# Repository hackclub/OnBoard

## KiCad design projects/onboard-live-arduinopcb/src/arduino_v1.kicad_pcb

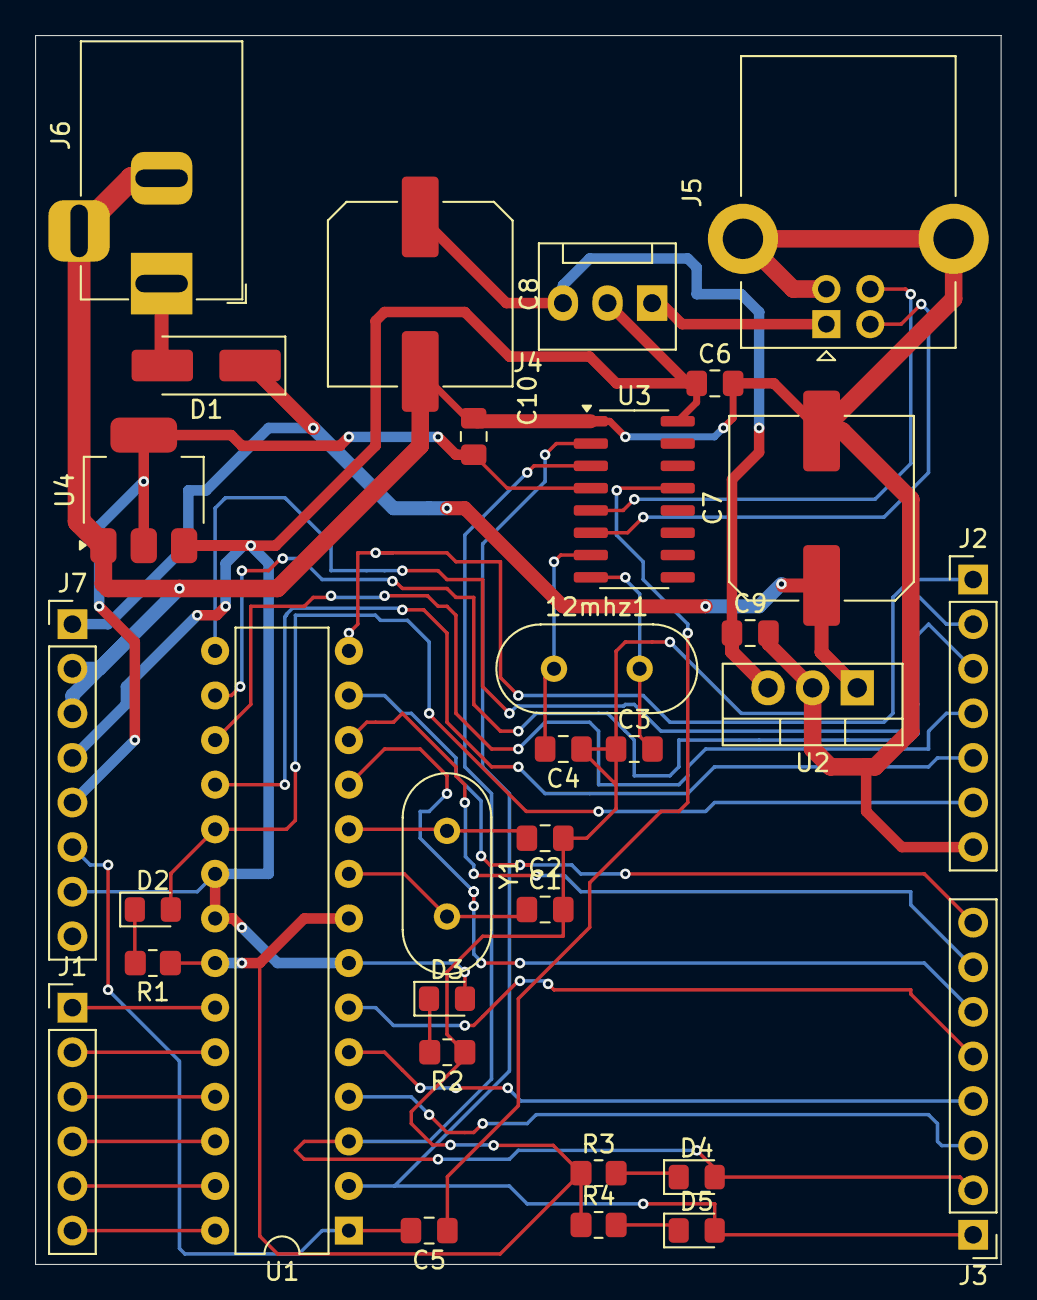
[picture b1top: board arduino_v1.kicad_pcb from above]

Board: 2 copper layers, 55.0 x 70.0 mm, 32 parts (0 on the bottom side), 39 nets.

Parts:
12mhz1: Crystal; Crystal_HC49-4H_Vertical
C1, C2, C3, C4: 22pf; C_0805_2012Metric_Pad1.18x1.45mm_HandSolder
C5, C6, C9, C10: 100nF; C_0805_2012Metric_Pad1.18x1.45mm_HandSolder
C7, C8: 100uF; C_Elec_10x10.2
D1: IN4007; D_SMA_Handsoldering
D2, D3, D4, D5: LED; LED_0805_2012Metric_Pad1.15x1.40mm_HandSolder
J1: Conn_01x06_Pin; PinHeader_1x06_P2.54mm_Vertical
J2: Conn_01x07_Pin; PinHeader_1x07_P2.54mm_Vertical
J3, J7: Conn_01x08_Pin; PinHeader_1x08_P2.54mm_Vertical
J4: Conn_01x03_Pin; FanPinHeader_1x03_P2.54mm_Vertical
J5: USB_B; USB_B_Lumberg_2411_02_Horizontal
J6: Barrel_Jack_Switch; BarrelJack_Horizontal
R1, R2, R3, R4: 330R; R_0805_2012Metric_Pad1.20x1.40mm_HandSolder
U1: ATmega328-P; DIP-28_W7.62mm
U2: LM7805_TO220; TO-220-3_Vertical
U3: CH340G; SOIC-16_3.9x9.9mm_P1.27mm
U4: AMS1117-3.3; SOT-223-3_TabPin2
Y1: Crystal; Crystal_HC49-4H_Vertical

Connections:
3.3V: C10.1, J7.5, U3.4 (V3), U4.2 (VO)
5V: C8.1, C9.1, J4.3, U2.3 (VO)
5VU: J4.1, J5.1 (VBUS)
A0: J1.1, U1.23 (PC0)
A1: J1.2, U1.24 (PC1)
A2: J1.3, U1.25 (PC2)
A3: J1.4, U1.26 (PC3)
A4: J1.5, U1.27 (PC4)
A5: J1.6, U1.28 (PC5)
D2: J3.3, U1.4 (PD2)
D3: J3.4, U1.5 (PD3)
D4: J3.5, U1.6 (PD4)
D5: J3.6, U1.11 (PD5)
D6: J3.7, U1.12 (PD6)
D7: J3.8, U1.13 (PD7)
D8: J2.1, U1.14 (PB0)
D9: J2.2, U1.15 (PB1)
D10: J2.3, U1.16 (PB2)
D11: J2.4, U1.17 (PB3)
D12: J2.5, U1.18 (PB4)
D13: D2.2 (A), J2.6, U1.19 (PB5)
GND: C1.2, C2.1, C3.1, C4.1, C6.2, C7.2, C8.2, C9.2, C10.2, J2.7, J5.4 (GND), J5.5 (Shield), J6.2, J6.3, J7.2, J7.3, R1.1, R2.1, R3.1, R4.1, U1.8 (GND), U1.22 (GND), U2.2 (GND), U3.1 (GND), U4.1 (GND)
unnamed: D1.2 (A), J6.1
unnamed: D2.1 (K), R1.2
unnamed: D3.1 (K), R2.2
unnamed: D4.1 (K), R3.2
unnamed: D5.1 (K), R4.2
unnamed: J5.3 (D+), U3.5 (UD+)
unnamed: J5.2 (D-), U3.6 (UD-)
unnamed: C1.1, U1.9 (XTAL1/PB6), Y1.2
unnamed: C2.2, U1.10 (XTAL2/PB7), Y1.1
unnamed: 12mhz1.1, C4.2, U3.7 (XI)
unnamed: 12mhz1.2, C3.2, U3.8 (XO)
unnamed: C5.1, U3.13 (~DTR)
RST: C5.2, J7.6, U1.1 (~RESET/PC6)
RXD: D5.2 (A), J3.1, U1.2 (PD0), U3.2 (TXD)
TXD: D4.2 (A), J3.2, U1.3 (PD1), U3.3 (RXD)
VCC: C6.1, D3.2 (A), J4.2, J7.4, J7.7, U1.7 (VCC), U1.20 (AVCC), U1.21 (AREF), U3.16 (VCC), U4.3 (VI)
VIN: C7.1, D1.1 (K), J7.1, U2.1 (VI)

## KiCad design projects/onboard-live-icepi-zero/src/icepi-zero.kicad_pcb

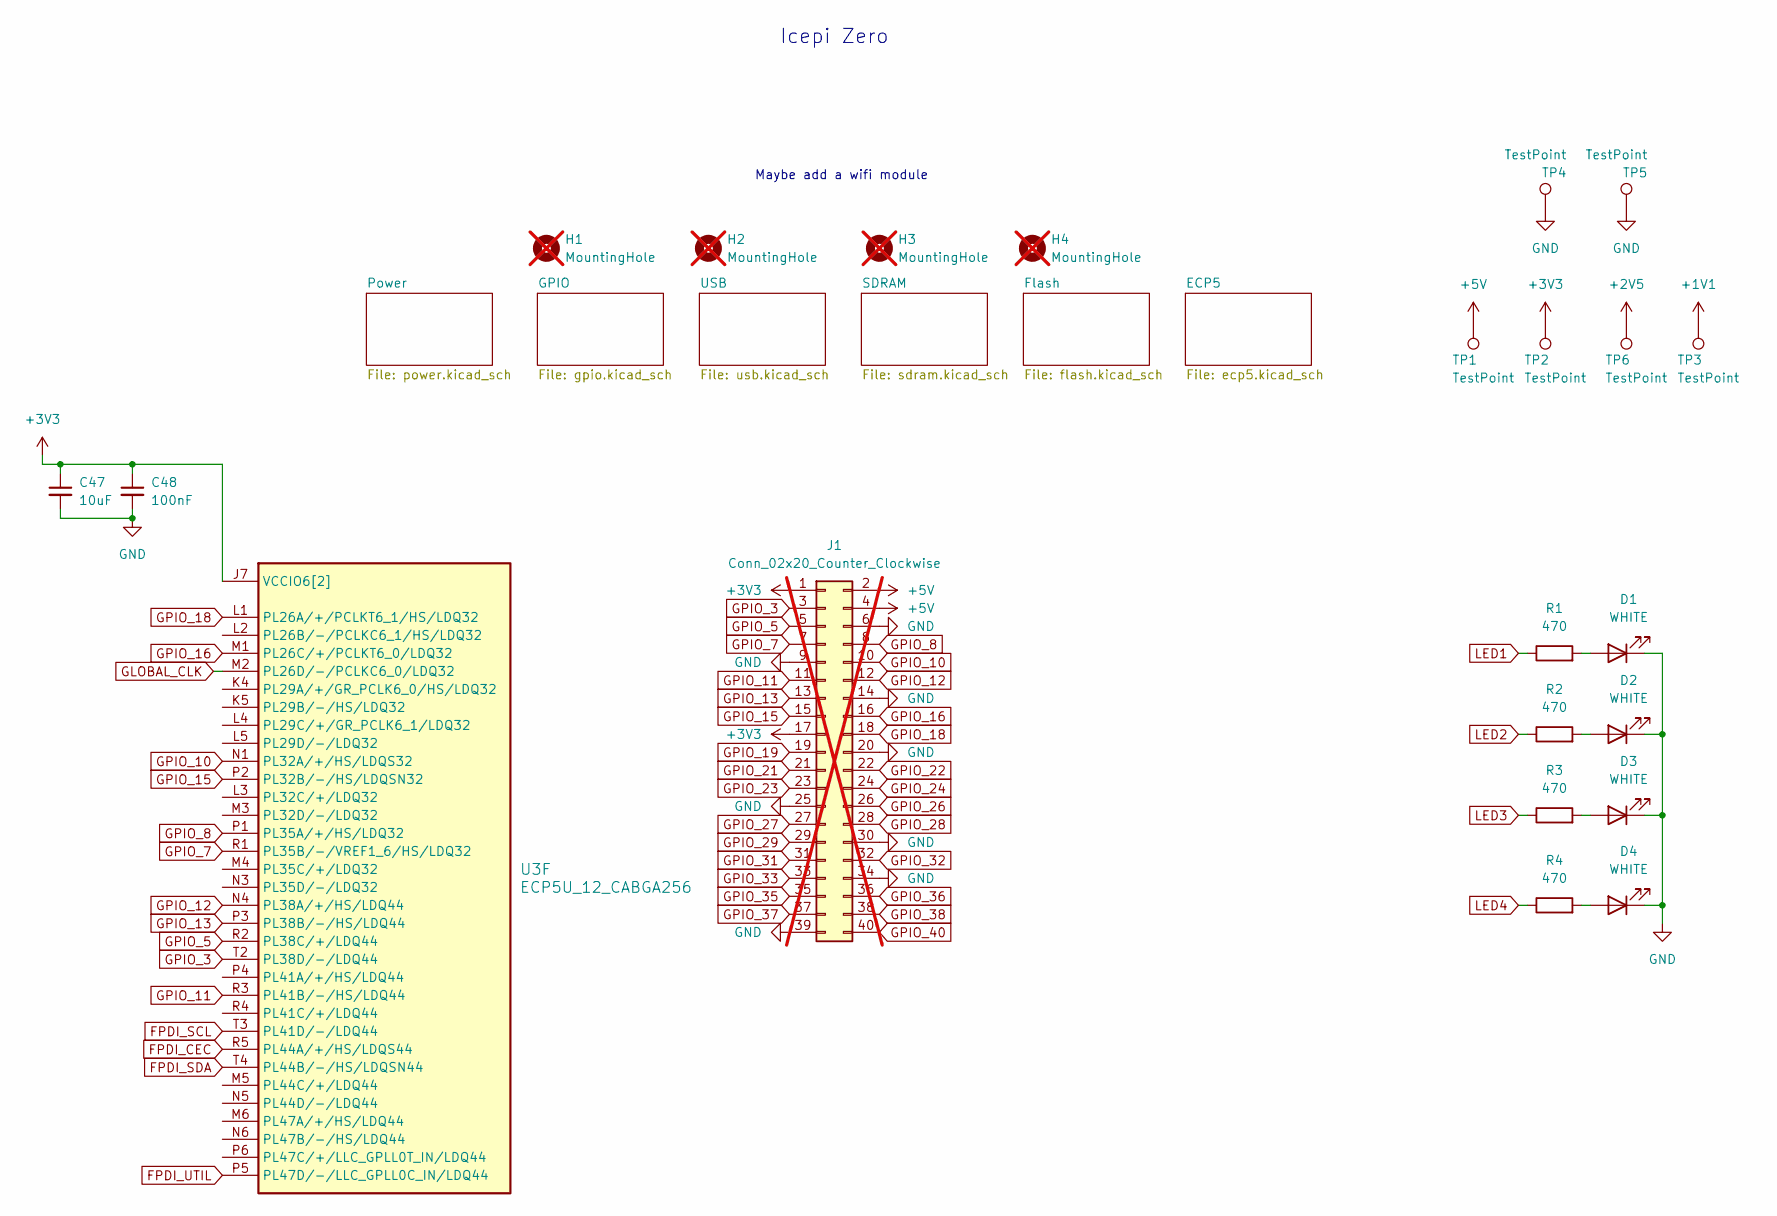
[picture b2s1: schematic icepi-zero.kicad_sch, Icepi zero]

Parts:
C47: 10uF; C_0603_1608Metric
C48: 100nF; C_0402_1005Metric; JLCPCB Part # C307331
D1, D2, D3, D4: WHITE; LED_0603_1608Metric; JLCPCB Part # C2290
H1, H2, H3, H4: MountingHole; MountingHole_2.5mm; not fitted
J1: Conn_02x20_Counter_Clockwise; PinHeader_2x20_P2.54mm_Vertical; not fitted
R1, R2, R3, R4: 470; R_0402_1005Metric; JLCPCB Part # C25117
TP1, TP2, TP3, TP4, TP5, TP6: TestPoint; TestPoint_Pad_D2.0mm
U3: ECP5U_12_CABGA256; BGA-256_14.0x14.0mm_Layout16x16_P0.8mm_Ball0.45mm_Pad0.32mm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; JLCPCB Part # C1521614

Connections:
+1V1: TP3.1; also elsewhere on the board
+2V5: TP6.1; also elsewhere on the board
+3V3: C47.1, C48.1, J1.1, J1.17, TP2.1, U3.J6 (VCCIO6[2]), U3.J7 (VCCIO6[2]); also elsewhere on the board
+5V: J1.2, J1.4, TP1.1; also elsewhere on the board
FPDI_CEC: U3.R5 (PL44A/+/HS/LDQS44); also elsewhere on the board
FPDI_SCL: U3.T3 (PL41D/-/LDQ44); also elsewhere on the board
FPDI_SDA: U3.T4 (PL44B/-/HS/LDQSN44); also elsewhere on the board
FPDI_UTIL: U3.P5 (PL47D/-/LLC_GPLL0C_IN/LDQ44); also elsewhere on the board
GLOBAL_CLK: U3.M2 (PL26D/-/PCLKC6_0/LDQ32); also elsewhere on the board
GND: C47.2, C48.2, D1.1 (K), D2.1 (K), D3.1 (K), D4.1 (K), J1.6, J1.9, J1.14, J1.20, J1.25, J1.30, J1.34, J1.39, TP4.1, TP5.1; also elsewhere on the board
GPIO_3: J1.3, U3.T2 (PL38D/-/LDQ44)
GPIO_5: J1.5, U3.R2 (PL38C/+/LDQ44)
GPIO_7: J1.7, U3.R1 (PL35B/-/VREF1_6/HS/LDQ32)
GPIO_8: J1.8, U3.P1 (PL35A/+/HS/LDQ32)
GPIO_10: J1.10, U3.N1 (PL32A/+/HS/LDQS32)
GPIO_11: J1.11, U3.R3 (PL41B/-/HS/LDQ44)
GPIO_12: J1.12, U3.N4 (PL38A/+/HS/LDQ44)
GPIO_13: J1.13, U3.P3 (PL38B/-/HS/LDQ44)
GPIO_15: J1.15, U3.P2 (PL32B/-/HS/LDQSN32)
GPIO_16: J1.16, U3.M1 (PL26C/+/PCLKT6_0/LDQ32)
GPIO_18: J1.18, U3.L1 (PL26A/+/PCLKT6_1/HS/LDQ32)
GPIO_19: J1.19; also elsewhere on the board
GPIO_21: J1.21; also elsewhere on the board
GPIO_22: J1.22; also elsewhere on the board
GPIO_23: J1.23; also elsewhere on the board
GPIO_24: J1.24; also elsewhere on the board
GPIO_26: J1.26; also elsewhere on the board
GPIO_27: J1.27; also elsewhere on the board
GPIO_28: J1.28; also elsewhere on the board
GPIO_29: J1.29; also elsewhere on the board
GPIO_31: J1.31; also elsewhere on the board
GPIO_32: J1.32; also elsewhere on the board
GPIO_33: J1.33; also elsewhere on the board
GPIO_35: J1.35; also elsewhere on the board
GPIO_36: J1.36; also elsewhere on the board
GPIO_37: J1.37; also elsewhere on the board
GPIO_38: J1.38; also elsewhere on the board
GPIO_40: J1.40; also elsewhere on the board
LED1: R1.1; also elsewhere on the board
LED2: R2.1; also elsewhere on the board
LED3: R3.1; also elsewhere on the board
LED4: R4.1; also elsewhere on the board
unnamed: D1.2 (A), R1.2
unnamed: D2.2 (A), R2.2
unnamed: D3.2 (A), R3.2
unnamed: D4.2 (A), R4.2

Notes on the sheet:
Icepi Zero
Maybe add a wifi module

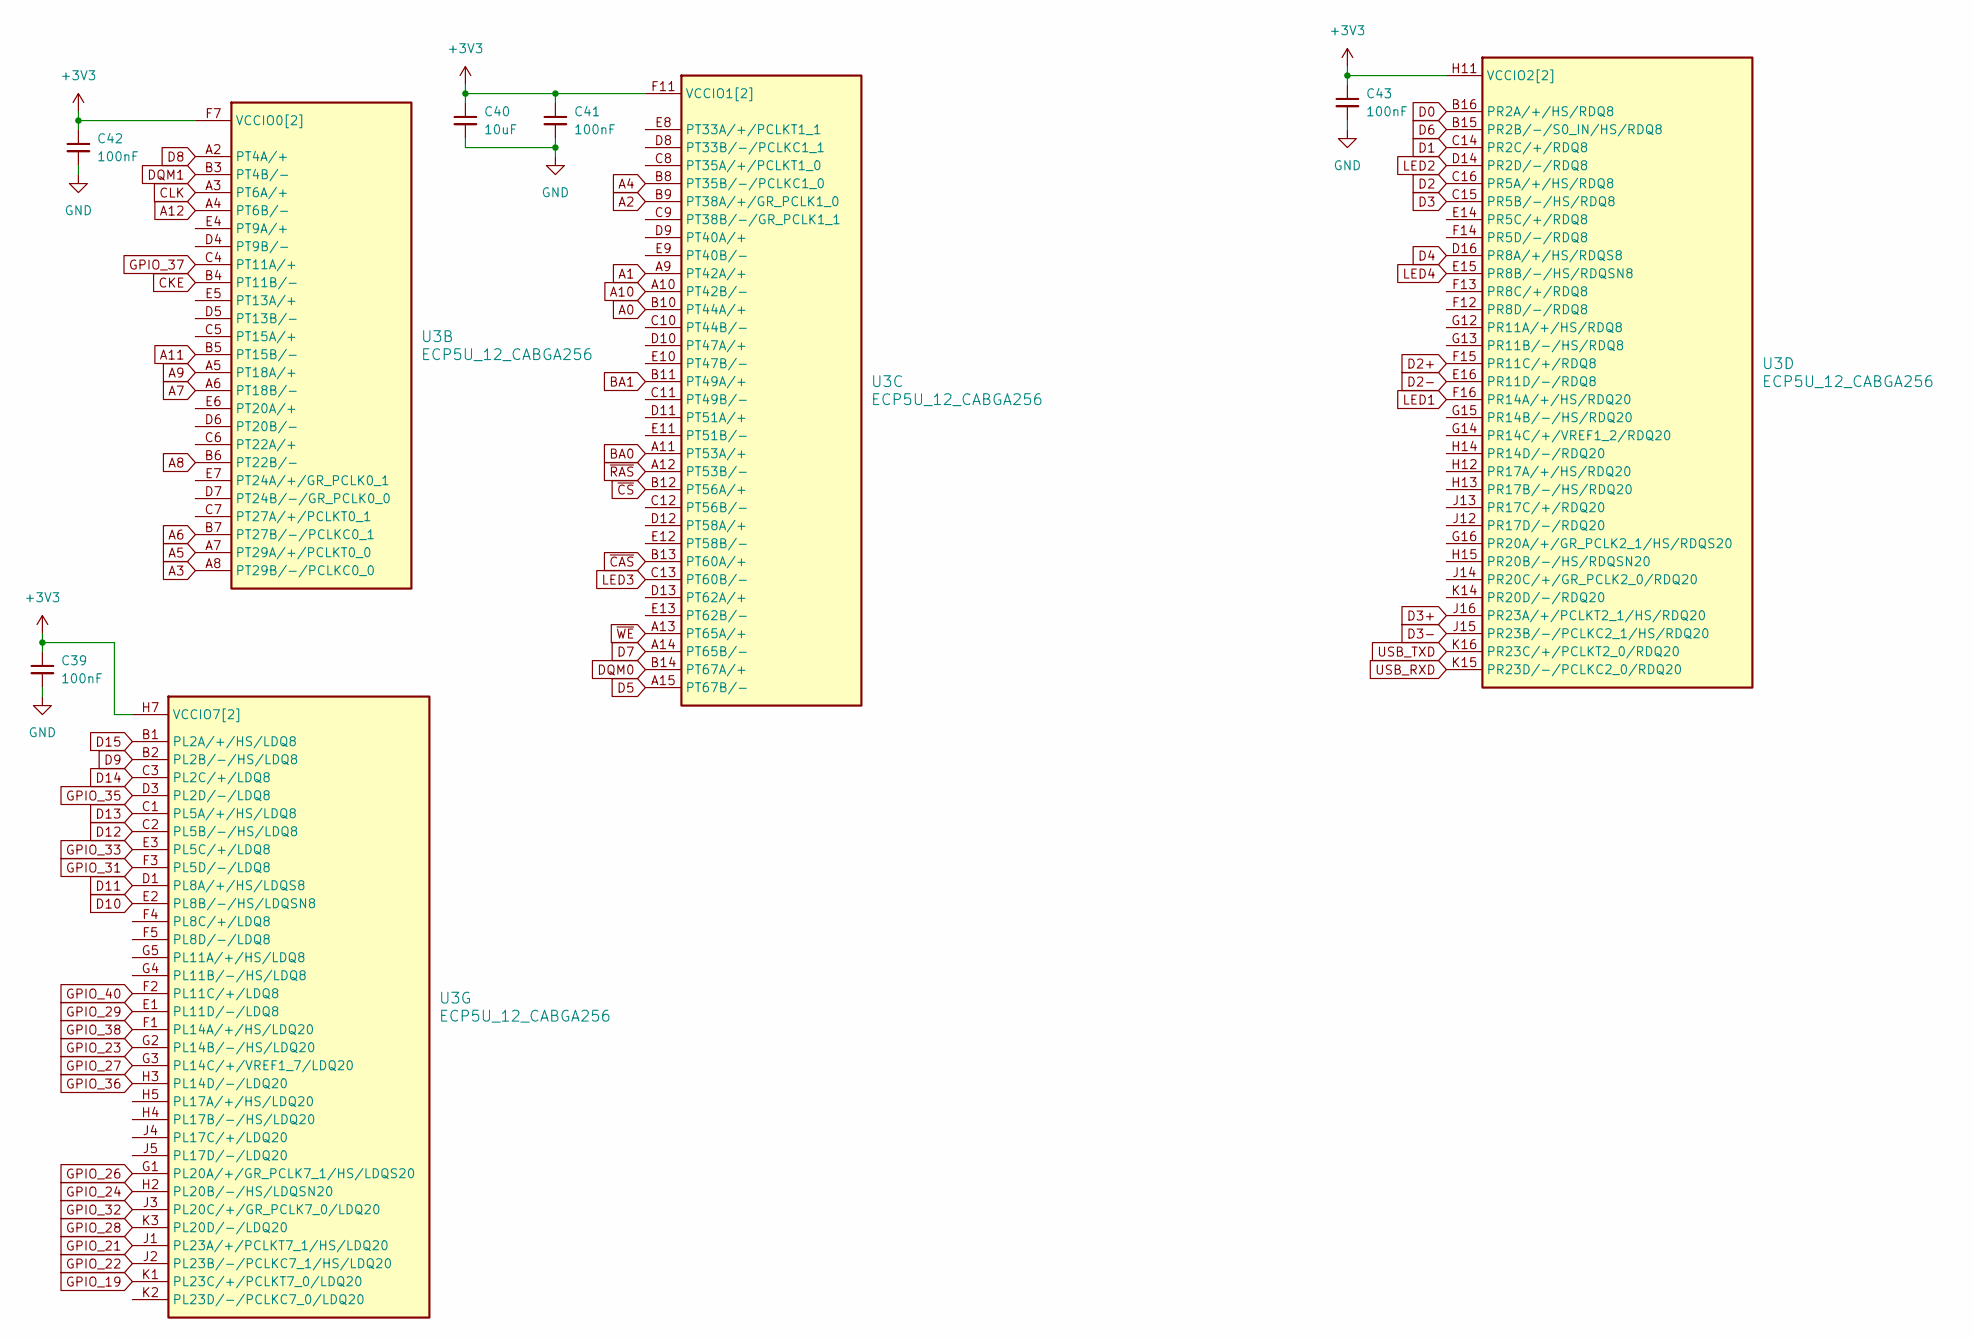
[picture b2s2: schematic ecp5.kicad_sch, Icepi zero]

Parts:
C39, C41, C42, C43: 100nF; C_0402_1005Metric; JLCPCB Part # C307331
C40: 10uF; C_0603_1608Metric
U3: ECP5U_12_CABGA256; BGA-256_14.0x14.0mm_Layout16x16_P0.8mm_Ball0.45mm_Pad0.32mm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; JLCPCB Part # C1521614

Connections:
+3V3: C39.1, C40.1, C41.1, C42.1, C43.1, U3.F6 (VCCIO0[2]), U3.F7 (VCCIO0[2]), U3.F10 (VCCIO1[2]), U3.F11 (VCCIO1[2]), U3.H6 (VCCIO7[2]), U3.H7 (VCCIO7[2]), U3.H11 (VCCIO2[2]), U3.J11 (VCCIO2[2]); also elsewhere on the board
A0: U3.B10 (PT44A/+); also elsewhere on the board
A1: U3.A9 (PT42A/+); also elsewhere on the board
A2: U3.B9 (PT38A/+/GR_PCLK1_0); also elsewhere on the board
A3: U3.A8 (PT29B/-/PCLKC0_0); also elsewhere on the board
A4: U3.B8 (PT35B/-/PCLKC1_0); also elsewhere on the board
A5: U3.A7 (PT29A/+/PCLKT0_0); also elsewhere on the board
A6: U3.B7 (PT27B/-/PCLKC0_1); also elsewhere on the board
A7: U3.A6 (PT18B/-); also elsewhere on the board
A8: U3.B6 (PT22B/-); also elsewhere on the board
A9: U3.A5 (PT18A/+); also elsewhere on the board
A10: U3.A10 (PT42B/-); also elsewhere on the board
A11: U3.B5 (PT15B/-); also elsewhere on the board
A12: U3.A4 (PT6B/-); also elsewhere on the board
BA0: U3.A11 (PT53A/+); also elsewhere on the board
BA1: U3.B11 (PT49A/+); also elsewhere on the board
CKE: U3.B4 (PT11B/-); also elsewhere on the board
CLK: U3.A3 (PT6A/+); also elsewhere on the board
D0: U3.B16 (PR2A/+/HS/RDQ8); also elsewhere on the board
D1: U3.C14 (PR2C/+/RDQ8); also elsewhere on the board
D2: U3.C16 (PR5A/+/HS/RDQ8); also elsewhere on the board
D2+: U3.F15 (PR11C/+/RDQ8); also elsewhere on the board
D2-: U3.E16 (PR11D/-/RDQ8); also elsewhere on the board
D3: U3.C15 (PR5B/-/HS/RDQ8); also elsewhere on the board
D3+: U3.J16 (PR23A/+/PCLKT2_1/HS/RDQ20); also elsewhere on the board
D3-: U3.J15 (PR23B/-/PCLKC2_1/HS/RDQ20); also elsewhere on the board
D4: U3.D16 (PR8A/+/HS/RDQS8); also elsewhere on the board
D5: U3.A15 (PT67B/-); also elsewhere on the board
D6: U3.B15 (PR2B/-/S0_IN/HS/RDQ8); also elsewhere on the board
D7: U3.A14 (PT65B/-); also elsewhere on the board
D8: U3.A2 (PT4A/+); also elsewhere on the board
D9: U3.B2 (PL2B/-/HS/LDQ8); also elsewhere on the board
D10: U3.E2 (PL8B/-/HS/LDQSN8); also elsewhere on the board
D11: U3.D1 (PL8A/+/HS/LDQS8); also elsewhere on the board
D12: U3.C2 (PL5B/-/HS/LDQ8); also elsewhere on the board
D13: U3.C1 (PL5A/+/HS/LDQ8); also elsewhere on the board
D14: U3.C3 (PL2C/+/LDQ8); also elsewhere on the board
D15: U3.B1 (PL2A/+/HS/LDQ8); also elsewhere on the board
DQM0: U3.B14 (PT67A/+); also elsewhere on the board
DQM1: U3.B3 (PT4B/-); also elsewhere on the board
GND: C39.2, C40.2, C41.2, C42.2, C43.2; also elsewhere on the board
GPIO_19: U3.K1 (PL23C/+/PCLKT7_0/LDQ20); also elsewhere on the board
GPIO_21: U3.J1 (PL23A/+/PCLKT7_1/HS/LDQ20); also elsewhere on the board
GPIO_22: U3.J2 (PL23B/-/PCLKC7_1/HS/LDQ20); also elsewhere on the board
GPIO_23: U3.G2 (PL14B/-/HS/LDQ20); also elsewhere on the board
GPIO_24: U3.H2 (PL20B/-/HS/LDQSN20); also elsewhere on the board
GPIO_26: U3.G1 (PL20A/+/GR_PCLK7_1/HS/LDQS20); also elsewhere on the board
GPIO_27: U3.G3 (PL14C/+/VREF1_7/LDQ20); also elsewhere on the board
GPIO_28: U3.K3 (PL20D/-/LDQ20); also elsewhere on the board
GPIO_29: U3.E1 (PL11D/-/LDQ8); also elsewhere on the board
GPIO_31: U3.F3 (PL5D/-/LDQ8); also elsewhere on the board
GPIO_32: U3.J3 (PL20C/+/GR_PCLK7_0/LDQ20); also elsewhere on the board
GPIO_33: U3.E3 (PL5C/+/LDQ8); also elsewhere on the board
GPIO_35: U3.D3 (PL2D/-/LDQ8); also elsewhere on the board
GPIO_36: U3.H3 (PL14D/-/LDQ20); also elsewhere on the board
GPIO_37: U3.C4 (PT11A/+); also elsewhere on the board
GPIO_38: U3.F1 (PL14A/+/HS/LDQ20); also elsewhere on the board
GPIO_40: U3.F2 (PL11C/+/LDQ8); also elsewhere on the board
LED1: U3.F16 (PR14A/+/HS/RDQ20); also elsewhere on the board
LED2: U3.D14 (PR2D/-/RDQ8); also elsewhere on the board
LED3: U3.C13 (PT60B/-); also elsewhere on the board
LED4: U3.E15 (PR8B/-/HS/RDQSN8); also elsewhere on the board
USB_RXD: U3.K15 (PR23D/-/PCLKC2_0/RDQ20); also elsewhere on the board
USB_TXD: U3.K16 (PR23C/+/PCLKT2_0/RDQ20); also elsewhere on the board
~CAS: U3.B13 (PT60A/+); also elsewhere on the board
~CS: U3.B12 (PT56A/+); also elsewhere on the board
~RAS: U3.A12 (PT53B/-); also elsewhere on the board
~WE: U3.A13 (PT65A/+); also elsewhere on the board

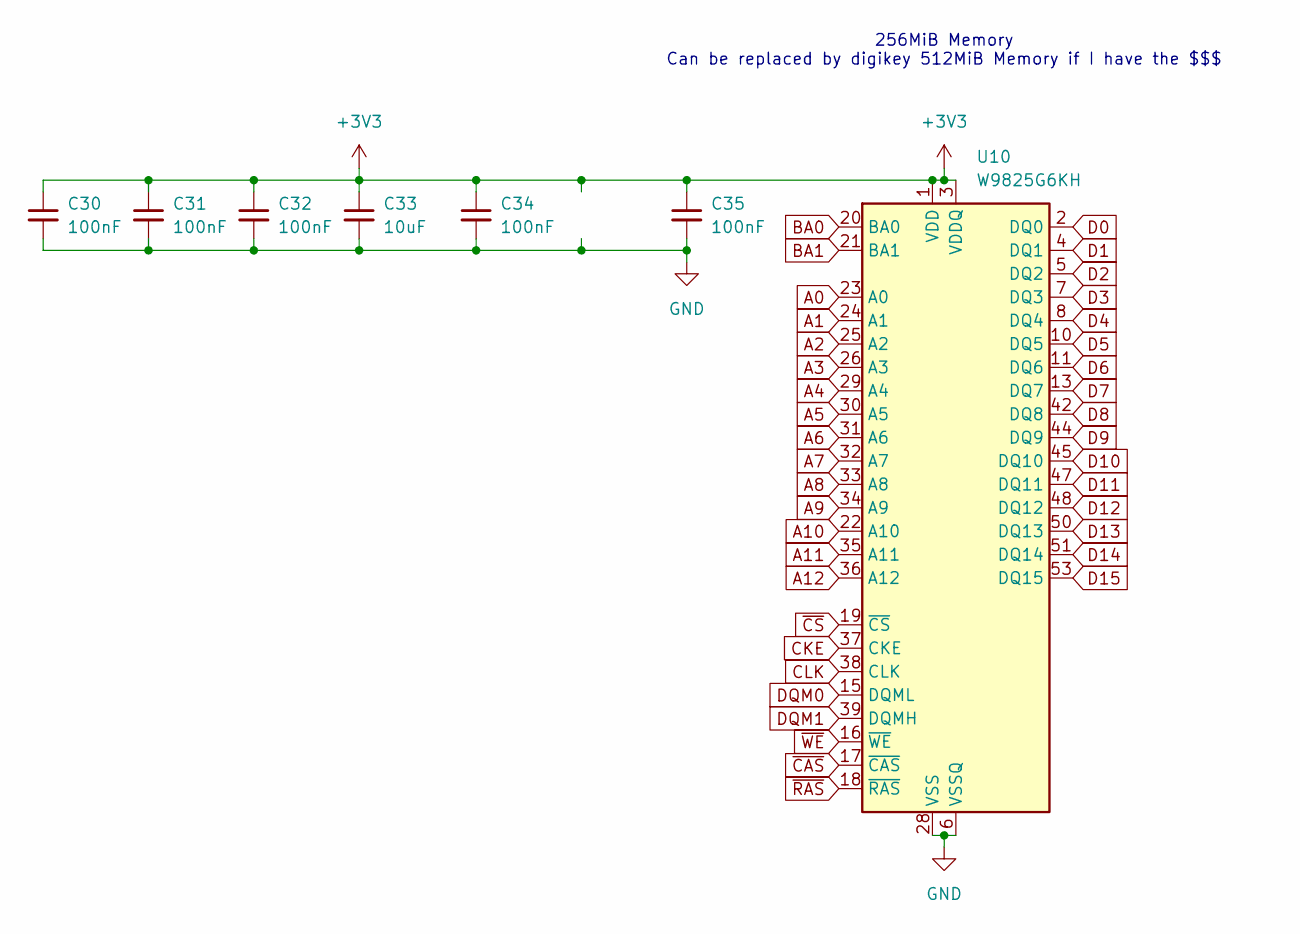
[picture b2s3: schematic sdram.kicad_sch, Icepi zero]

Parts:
C30, C31, C32, C34, C35: 100nF; C_0402_1005Metric; JLCPCB Part # C307331
C33: 10uF; C_0603_1608Metric
U10: W9825G6KH; TSOP-II-54_22.2x10.16mm_P0.8mm; JLCPCB Part # C62246

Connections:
+3V3: C30.1, C31.1, C32.1, C33.1, C34.1, C35.1, U10.1 (VDD), U10.3 (VDDQ), U10.9 (VDDQ), U10.14 (VDD), U10.27 (VDD), U10.43 (VDDQ), U10.49 (VDDQ); also elsewhere on the board
A0: U10.23 (A0); also elsewhere on the board
A1: U10.24 (A1); also elsewhere on the board
A2: U10.25 (A2); also elsewhere on the board
A3: U10.26 (A3); also elsewhere on the board
A4: U10.29 (A4); also elsewhere on the board
A5: U10.30 (A5); also elsewhere on the board
A6: U10.31 (A6); also elsewhere on the board
A7: U10.32 (A7); also elsewhere on the board
A8: U10.33 (A8); also elsewhere on the board
A9: U10.34 (A9); also elsewhere on the board
A10: U10.22 (A10); also elsewhere on the board
A11: U10.35 (A11); also elsewhere on the board
A12: U10.36 (A12); also elsewhere on the board
BA0: U10.20 (BA0); also elsewhere on the board
BA1: U10.21 (BA1); also elsewhere on the board
CKE: U10.37 (CKE); also elsewhere on the board
CLK: U10.38 (CLK); also elsewhere on the board
D0: U10.2 (DQ0); also elsewhere on the board
D1: U10.4 (DQ1); also elsewhere on the board
D2: U10.5 (DQ2); also elsewhere on the board
D3: U10.7 (DQ3); also elsewhere on the board
D4: U10.8 (DQ4); also elsewhere on the board
D5: U10.10 (DQ5); also elsewhere on the board
D6: U10.11 (DQ6); also elsewhere on the board
D7: U10.13 (DQ7); also elsewhere on the board
D8: U10.42 (DQ8); also elsewhere on the board
D9: U10.44 (DQ9); also elsewhere on the board
D10: U10.45 (DQ10); also elsewhere on the board
D11: U10.47 (DQ11); also elsewhere on the board
D12: U10.48 (DQ12); also elsewhere on the board
D13: U10.50 (DQ13); also elsewhere on the board
D14: U10.51 (DQ14); also elsewhere on the board
D15: U10.53 (DQ15); also elsewhere on the board
DQM0: U10.15 (DQML); also elsewhere on the board
DQM1: U10.39 (DQMH); also elsewhere on the board
GND: C30.2, C31.2, C32.2, C33.2, C34.2, C35.2, U10.6 (VSSQ), U10.12 (VSSQ), U10.28 (VSS), U10.41 (VSS), U10.46 (VSSQ), U10.52 (VSSQ), U10.54 (VSS); also elsewhere on the board
~CAS: U10.17 (~CAS); also elsewhere on the board
~CS: U10.19 (~CS); also elsewhere on the board
~RAS: U10.18 (~RAS); also elsewhere on the board
~WE: U10.16 (~WE); also elsewhere on the board

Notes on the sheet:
256MiB Memory Can be replaced by digikey 512MiB Memory if I have the $$$

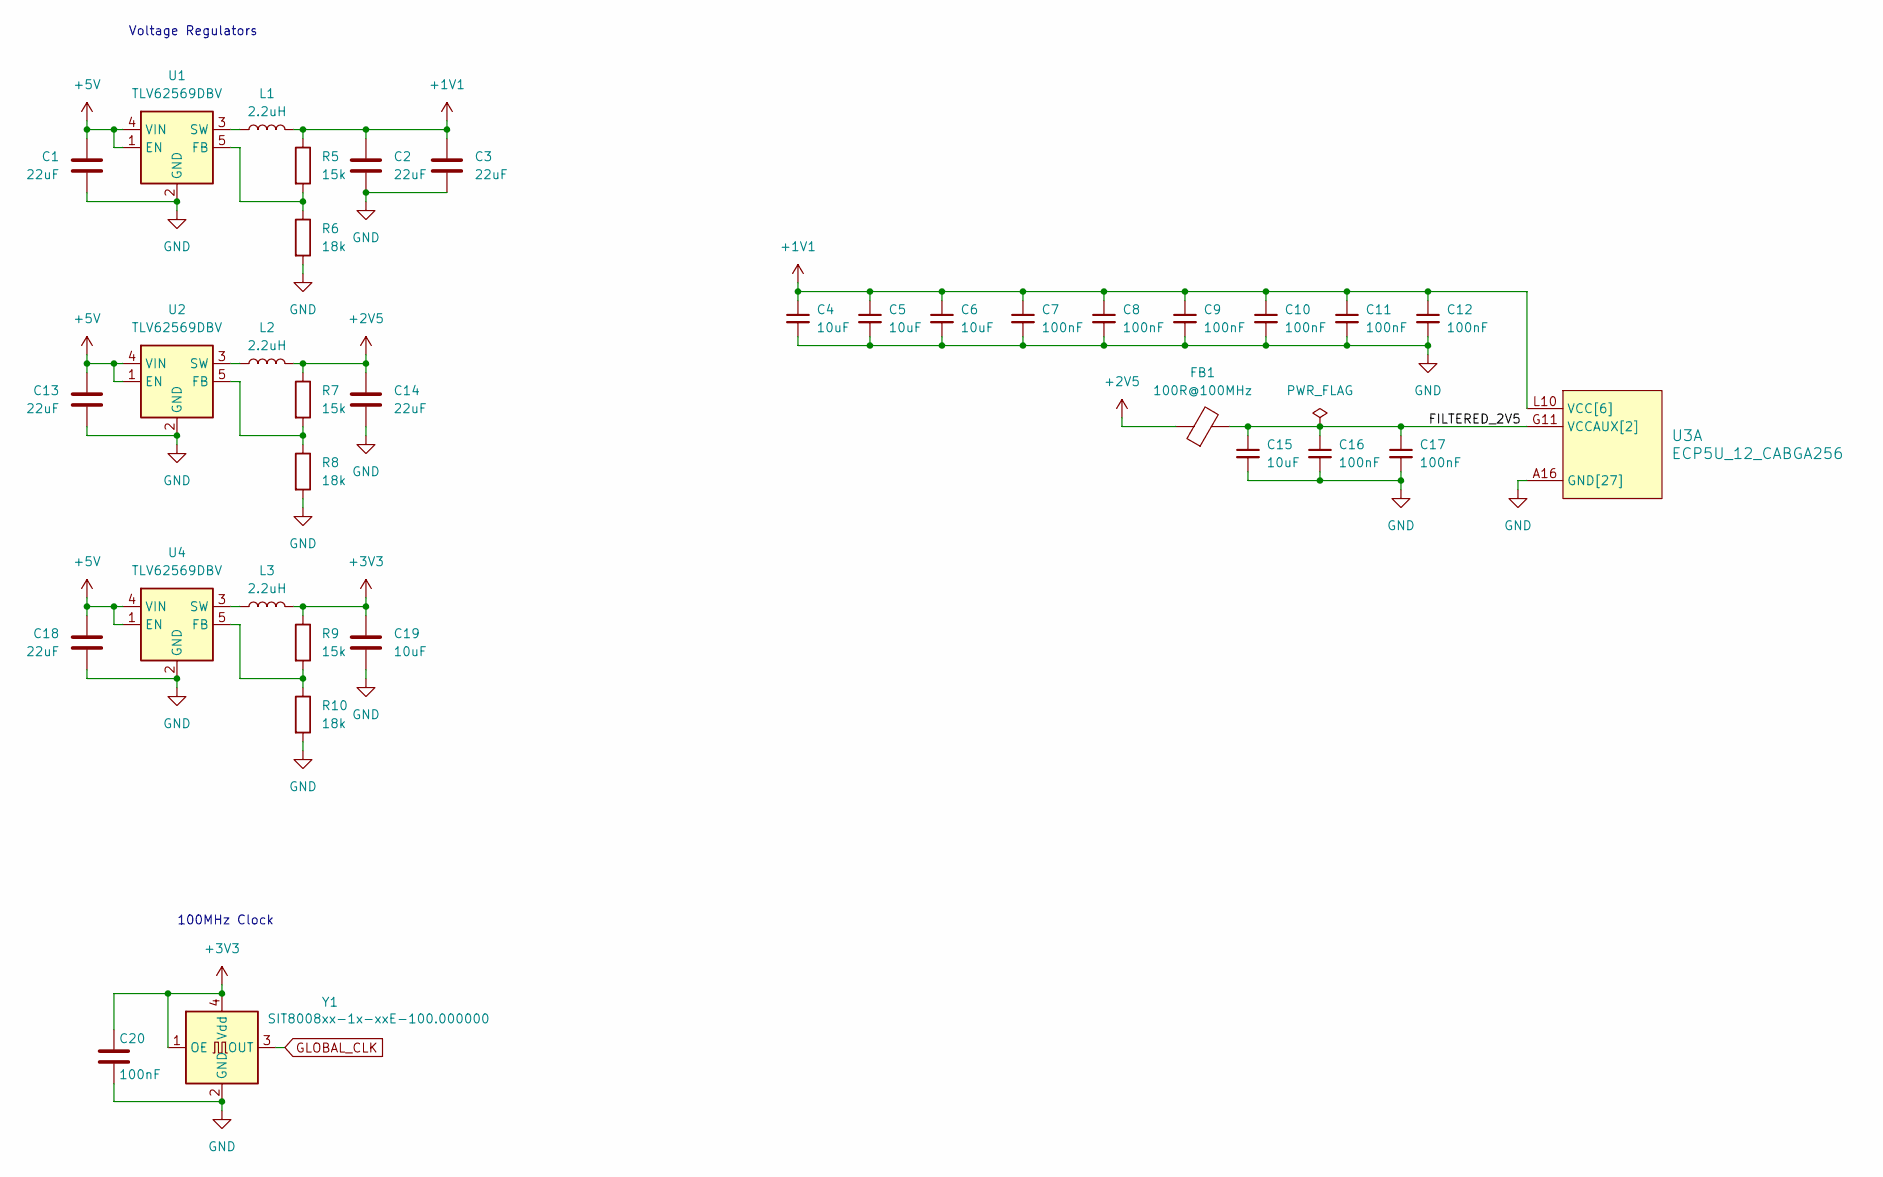
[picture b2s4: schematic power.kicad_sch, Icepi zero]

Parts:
C1, C2, C3, C13, C14, C18: 22uF; C_0603_1608Metric; JLCPCB Part # C59461
C4, C5, C6, C15, C19: 10uF; C_0603_1608Metric
C7, C8, C9, C10, C11, C12, C16, C17, C20: 100nF; C_0402_1005Metric; JLCPCB Part # C307331
FB1: 100R@100MHz; L_0805_2012Metric; JLCPCB Part # C1015
L1, L2, L3: 2.2uH; L_0805_2012Metric; JLCPCB Part # C1043
R5, R7, R9: 15k; R_0402_1005Metric; JLCPCB Part # C25756
R6, R8, R10: 18k; R_0402_1005Metric; JLCPCB Part # C25762
U1, U2, U4: TLV62569DBV; SOT-23-5; JLCPCB Part # C141836
U3: ECP5U_12_CABGA256; BGA-256_14.0x14.0mm_Layout16x16_P0.8mm_Ball0.45mm_Pad0.32mm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; JLCPCB Part # C1521614
Y1: SIT8008xx-1x-xxE-100.000000; Oscillator_SMD_SiT_PQFN-4Pin_2.5x2.0mm; JLCPCB Part # C17281729

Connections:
+1V1: C2.1, C3.1, C4.1, C5.1, C6.1, C7.1, C8.1, C9.1, C10.1, C11.1, C12.1, L1.2, R5.1, U3.G6 (VCC[6]), U3.G7 (VCC[6]), U3.G9 (VCC[6]), U3.L8 (VCC[6]), U3.L9 (VCC[6]), U3.L10 (VCC[6]); also elsewhere on the board
+2V5: C14.1, FB1.1, L2.2, R7.1; also elsewhere on the board
+3V3: C19.1, C20.1, L3.2, R9.1, Y1.1 (OE), Y1.4 (Vdd); also elsewhere on the board
+5V: C1.1, C13.1, C18.1, U1.1 (EN), U1.4 (VIN), U2.1 (EN), U2.4 (VIN), U4.1 (EN), U4.4 (VIN); also elsewhere on the board
/Power/FILTERED_2V5: C15.1, C16.1, C17.1, FB1.2, U3.G11 (VCCAUX[2]), U3.L7 (VCCAUX[2])
GLOBAL_CLK: Y1.3 (OUT); also elsewhere on the board
GND: C1.2, C2.2, C3.2, C4.2, C5.2, C6.2, C7.2, C8.2, C9.2, C10.2, C11.2, C12.2, C13.2, C14.2, C15.2, C16.2, C17.2, C18.2, C19.2, C20.2, R6.2, R8.2, R10.2, U1.2 (GND), U2.2 (GND), U3.A1 (GND[27]), U3.A16 (GND[27]), U3.D2 (GND[27]), U3.D15 (GND[27]), U3.F8 (GND[27]), U3.F9 (GND[27]), U3.G8 (GND[27]), U3.G10 (GND[27]), U3.H1 (GND[27]), U3.H8 (GND[27]), U3.H9 (GND[27]), U3.H10 (GND[27]), U3.H16 (GND[27]), U3.J8 (GND[27]), U3.J9 (GND[27]), U3.J10 (GND[27]), U3.K6 (GND[27]), U3.K7 (GND[27]), U3.K8 (GND[27]), U3.K9 (GND[27]), U3.K10 (GND[27]), U3.N2 (GND[27]), U3.N15 (GND[27]), U3.T1 (GND[27]), U3.T5 (GND[27]), U3.T12 (GND[27]), U3.T16 (GND[27]), U4.2 (GND), Y1.2 (GND); also elsewhere on the board
unnamed: R5.2, R6.1, U1.5 (FB)
unnamed: L1.1, U1.3 (SW)
unnamed: R7.2, R8.1, U2.5 (FB)
unnamed: L2.1, U2.3 (SW)
unnamed: R9.2, R10.1, U4.5 (FB)
unnamed: L3.1, U4.3 (SW)

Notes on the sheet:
100MHz Clock
Voltage Regulators

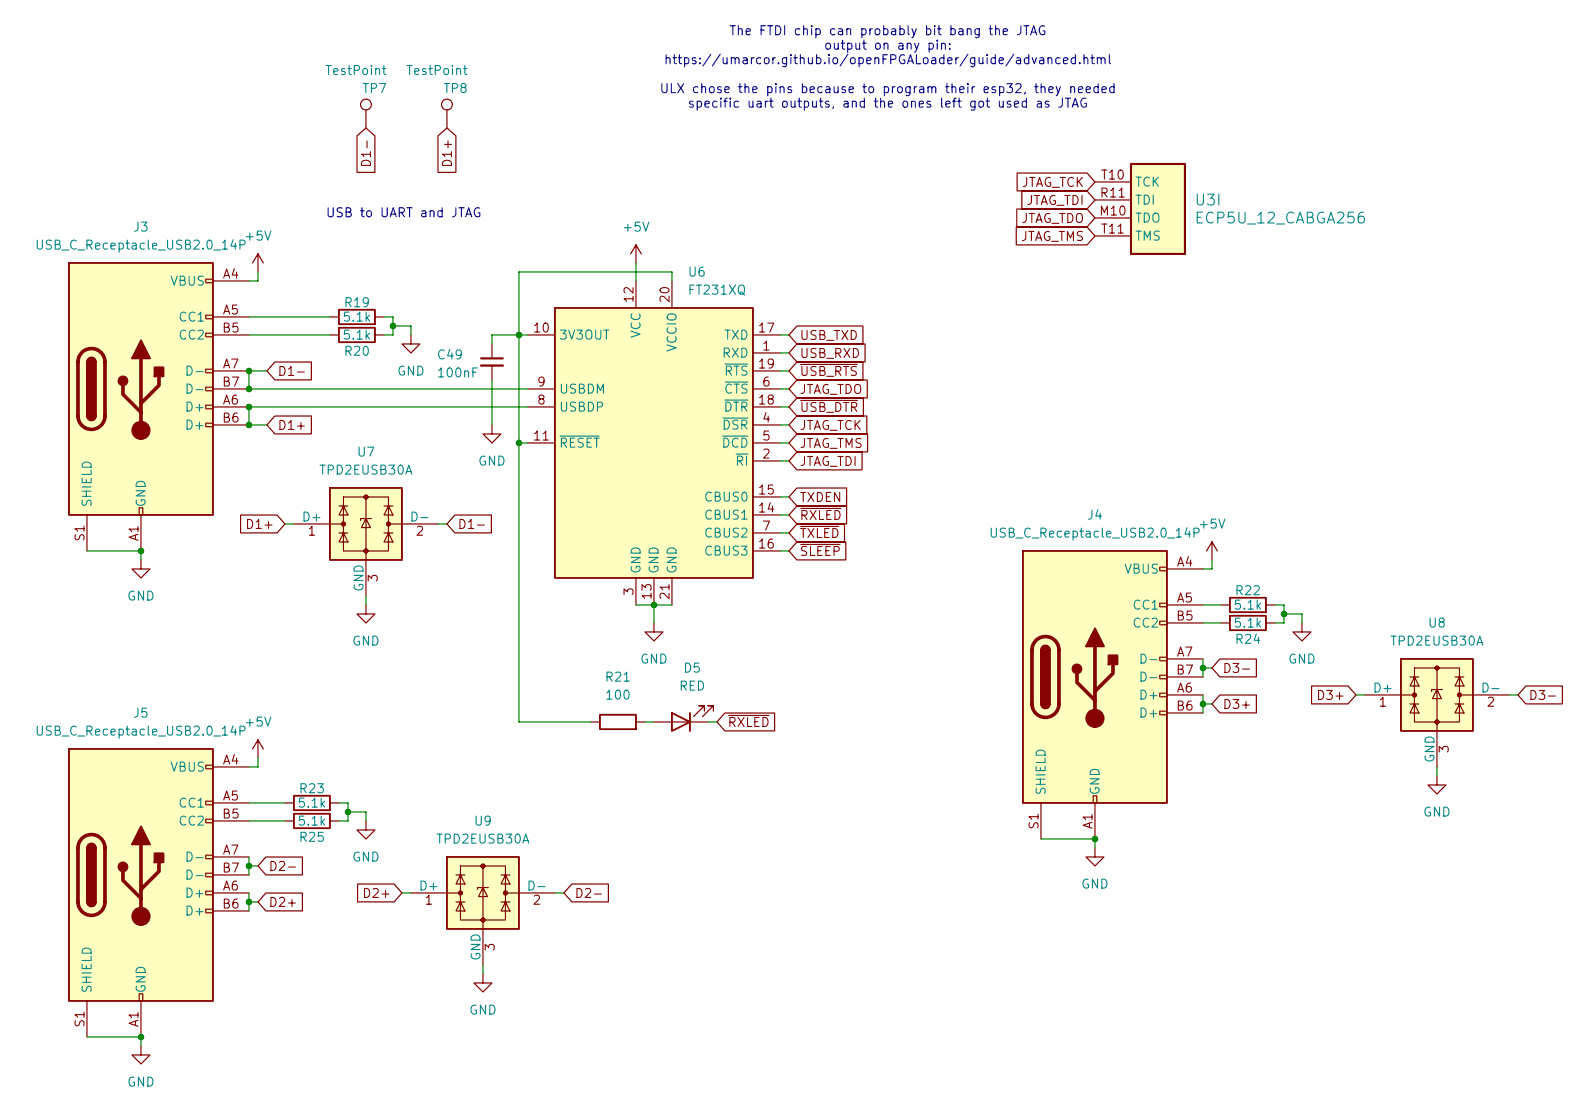
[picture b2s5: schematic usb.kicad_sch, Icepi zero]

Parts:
C49: 100nF; C_0402_1005Metric; JLCPCB Part # C307331
D5: RED; LED_0603_1608Metric; JLCPCB Part # C2286
J3, J4, J5: USB_C_Receptacle_USB2.0_14P; USB_C_Receptacle_GCT_USB4105-xx-A_16P_TopMnt_Horizontal; JLCPCB Part # C2765186
R19, R20, R22, R23, R24, R25: 5.1k; R_0402_1005Metric; JLCPCB Part # C25905
R21: 100; R_0402_1005Metric; JLCPCB Part # C25076
TP7, TP8: TestPoint; TestPoint_Pad_D2.0mm
U3: ECP5U_12_CABGA256; BGA-256_14.0x14.0mm_Layout16x16_P0.8mm_Ball0.45mm_Pad0.32mm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; JLCPCB Part # C1521614
U6: FT231XQ; QFN-20-1EP_4x4mm_P0.5mm_EP2.5x2.5mm; JLCPCB Part # C132159
U7, U8, U9: TPD2EUSB30A; Texas_DRT-3; JLCPCB Part # C3011197

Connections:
+5V: J3.A4 (VBUS), J3.A9 (VBUS), J3.B4 (VBUS), J3.B9 (VBUS), J4.A4 (VBUS), J4.A9 (VBUS), J4.B4 (VBUS), J4.B9 (VBUS), J5.A4 (VBUS), J5.A9 (VBUS), J5.B4 (VBUS), J5.B9 (VBUS), U6.12 (VCC); also elsewhere on the board
D1+: J3.A6 (D+), J3.B6 (D+), TP8.1, U6.8 (USBDP), U7.1 (D+)
D1-: J3.A7 (D-), J3.B7 (D-), TP7.1, U6.9 (USBDM), U7.2 (D-)
D2+: J5.A6 (D+), J5.B6 (D+), U9.1 (D+); also elsewhere on the board
D2-: J5.A7 (D-), J5.B7 (D-), U9.2 (D-); also elsewhere on the board
D3+: J4.A6 (D+), J4.B6 (D+), U8.1 (D+); also elsewhere on the board
D3-: J4.A7 (D-), J4.B7 (D-), U8.2 (D-); also elsewhere on the board
GND: C49.2, J3.A1 (GND), J3.A12 (GND), J3.B1 (GND), J3.B12 (GND), J3.S1 (SHIELD), J4.A1 (GND), J4.A12 (GND), J4.B1 (GND), J4.B12 (GND), J4.S1 (SHIELD), J5.A1 (GND), J5.A12 (GND), J5.B1 (GND), J5.B12 (GND), J5.S1 (SHIELD), R19.2, R20.1, R22.2, R23.2, R24.1, R25.1, U6.3 (GND), U6.13 (GND), U6.21 (GND), U7.3 (GND), U8.3 (GND), U9.3 (GND); also elsewhere on the board
JTAG_TCK: U3.T10 (TCK), U6.4 (~DSR)
JTAG_TDI: U3.R11 (TDI), U6.2 (~RI)
JTAG_TDO: U3.M10 (TDO), U6.6 (~CTS)
JTAG_TMS: U3.T11 (TMS), U6.5 (~DCD)
unnamed: D5.2 (A), R21.2
unnamed: J3.A5 (CC1), R19.1
unnamed: J3.B5 (CC2), R20.2
unnamed: J4.A5 (CC1), R22.1
unnamed: J4.B5 (CC2), R24.2
unnamed: J5.A5 (CC1), R23.1
unnamed: J5.B5 (CC2), R25.2
unnamed: C49.1, R21.1, U6.10 (3V3OUT), U6.11 (~RESET), U6.20 (VCCIO)
TXDEN: U6.15 (CBUS0)
USB_RXD: U6.1 (RXD); also elsewhere on the board
USB_TXD: U6.17 (TXD); also elsewhere on the board
~RXLED: D5.1 (K), U6.14 (CBUS1)
~SLEEP: U6.16 (CBUS3)
~TXLED: U6.7 (CBUS2)
~USB_DTR: U6.18 (~DTR); also elsewhere on the board
~USB_RTS: U6.19 (~RTS); also elsewhere on the board

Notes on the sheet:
USB to UART and JTAG
The FTDI chip can probably bit bang the JTAG output on any pin: https://umarcor.github.io/openFPGALoader/guide/advanced.html ULX chose the pins because to program their esp32, they needed specific uart outputs, and the ones left got used as JTAG
